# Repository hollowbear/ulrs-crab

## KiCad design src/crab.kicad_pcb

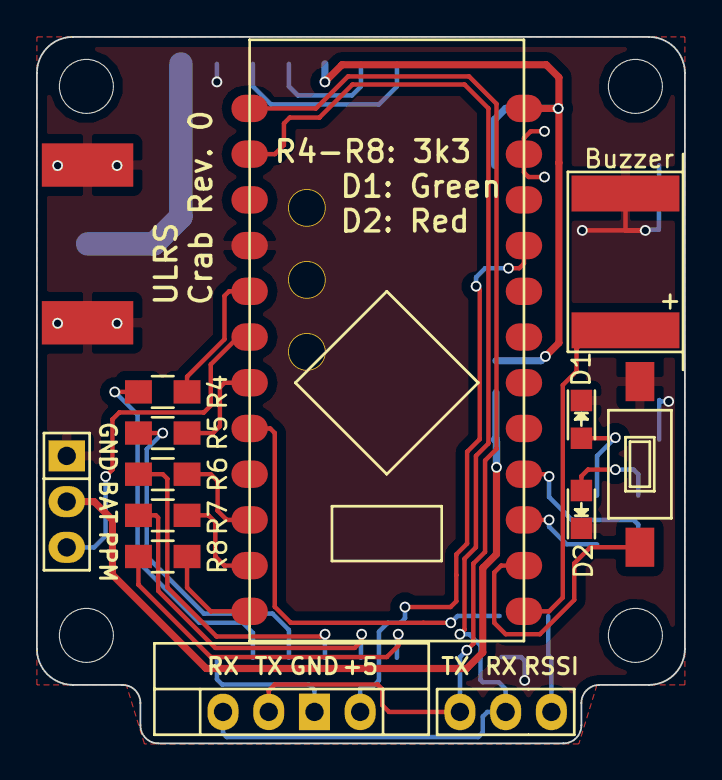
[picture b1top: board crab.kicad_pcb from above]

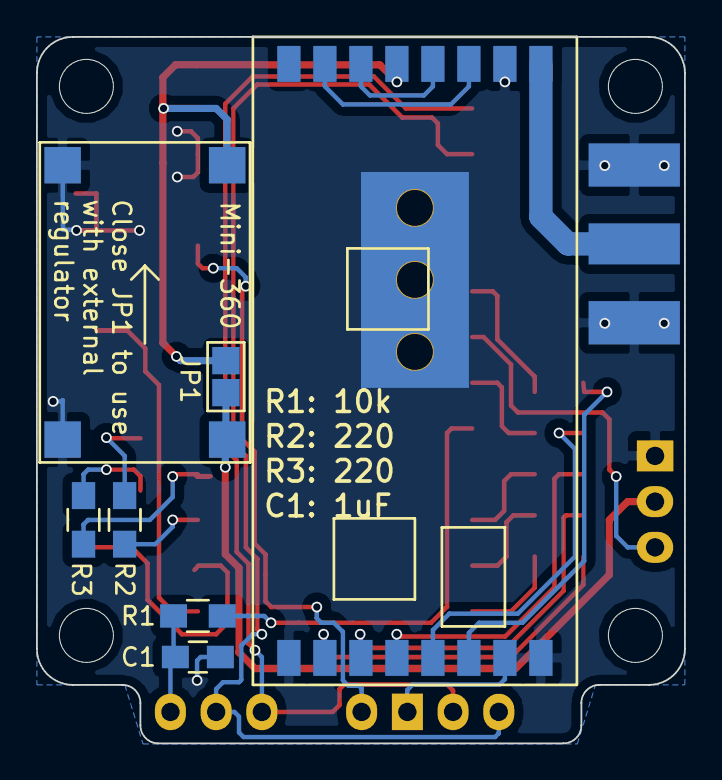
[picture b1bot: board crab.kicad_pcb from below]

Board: 2 copper layers, 36.0 x 39.2 mm, 21 parts (8 on the bottom side), 28 nets.

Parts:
C1: 1uF; C_0805_HandSoldering
D1: Green; LED_0805
D2: Red; LED_0805
JP1: Jumper_NO_Small; JUMPER_SMD
P1: CONN_01X03; Pin_Header_Straight_1x03
P2: CONN_01X03; Pin_Header_Straight_Uniform_1x03
P3: SMA; SMA_Edge
R1: 10k; R_0805_HandSoldering
R2, R3: 220; R_0805_HandSoldering
R4, R5, R6, R7, R8: 3k3; R_0805_HandSoldering
SP1: SPEAKER; Buzzer_12x9.5RM7.6_SMD
SW1: SW_PUSH; SW_SPST_FSMSM
U1: RFM23BP
U2: UBEC; Mini-360
U3: ArduinoProMini; ArduProMini-6_SMD
U4: HC-06

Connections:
+5V: U3.22, U4.1
+6V: JP1.2, U1.5, U2.3, U3.19
+BATT: JP1.1, P1.2, U2.1
BTN: SW1.1, U3.29
Buzz: SP1.1, U3.30
GND: C1.2, D1.1, D2.1, P1.1, P3.2, SP1.2, SW1.2, U1.2, U1.9, U1.15, U1.16, U2.2, U2.4, U3.10, U3.20, U4.2
unnamed: D1.2, R2.2
unnamed: D2.2, R3.2
unnamed: P3.1, U1.1
unnamed: R1.1, U3.14
unnamed: R2.1, U3.28
unnamed: R3.1, U3.27
unnamed: R4.2, U1.14
unnamed: R5.2, U1.13
unnamed: R6.2, U1.12
unnamed: R7.2, U1.11
unnamed: R8.2, U1.10
unnamed: U1.3, U1.7
unnamed: U1.4, U1.6
PPM: P1.3, U3.12
RSSI: C1.1, P2.1, R1.2
RX: P2.2, U3.8, U4.4
SCK: R6.1, U3.16
SDI: R7.1, U3.17
SDO: R8.1, U3.18
TX: P2.3, U3.7, U4.3
nIRQ: R4.1, U3.11
nSEL: R5.1, U3.13

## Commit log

2017-06-19 initial commit, faulty
